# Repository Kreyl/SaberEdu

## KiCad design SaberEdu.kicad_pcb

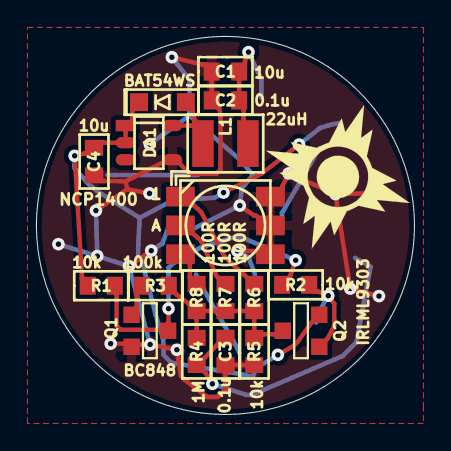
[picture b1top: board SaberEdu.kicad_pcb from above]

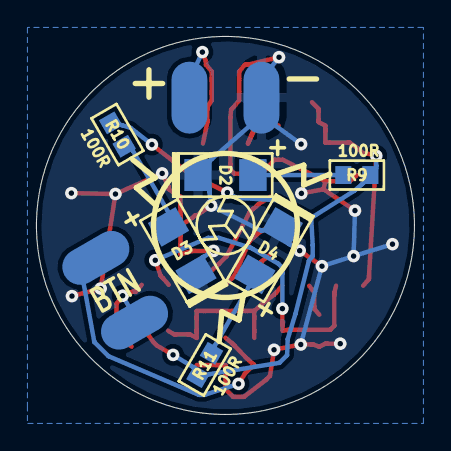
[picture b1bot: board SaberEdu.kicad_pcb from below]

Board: 2 copper layers, 21.0 x 21.0 mm, 29 parts (10 on the bottom side), 15 nets.

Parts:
C1, C4: 10u; CAP_0603
C2, C3: 0.1u; CAP_0603
D1: BAT54WS; SOD323
D2, D3, D4: LED; LED_1206
DA1: NCP1400; SOT23-5
L1: 22uH; IND_1210_LQH32C
Logo1: Logo; OldSithEmpire_6x6
Q1: BC848; SOT23-3
Q2: IRLML9303; SOT23-3
Q3: LED_5050
R1, R2, R5: 10k; RES_0603
R3: 100k; RES_0603
R4: 1M; RES_0603
R6, R7, R8, R9, R10, R11: 100R; RES_0603
XL1, XL2, XL3, XL4: CONN_1; Pad_2x4_Oval

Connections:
+3.3V: C4.2, D1.C, DA1.1, DA1.2, Q2.2, R1.1, R9.2, R10.2, R11.2
+BATT: C1.2, C2.2, L1.2, XL1.1
/CTRLED: Q2.3, R3.1, R4.1, R5.1, R6.2, R7.2, R8.2
/Lout: D1.A, DA1.5, L1.1
GND: C1.1, C2.1, C3.2, C4.1, D2.C, D3.C, D4.C, DA1.4, Q1.2, Q3.4, Q3.5, Q3.6, R5.2, XL2.1
unnamed: C3.1, R4.2, XL4.1
unnamed: D2.A, R9.1
unnamed: D3.A, R10.1
unnamed: D4.A, R11.1
unnamed: Q1.1, R3.2
unnamed: Q1.3, R1.2, R2.2
unnamed: Q2.1, R2.1, XL3.1
unnamed: Q3.1, R6.1
unnamed: Q3.2, R7.1
unnamed: Q3.3, R8.1

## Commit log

2018-07-23 + Sent to factory
